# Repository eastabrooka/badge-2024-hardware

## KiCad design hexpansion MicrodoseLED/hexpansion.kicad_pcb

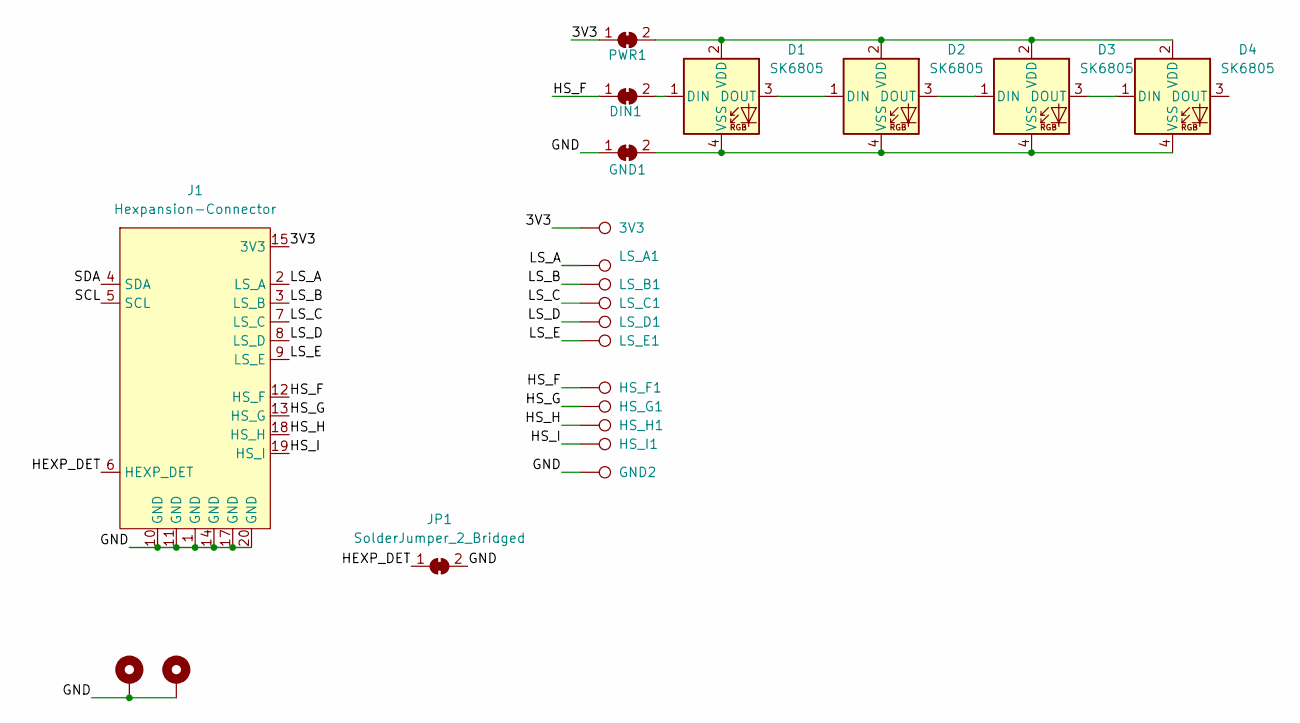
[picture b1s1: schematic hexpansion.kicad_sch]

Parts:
3V3: TestPoint; TestPoint_Pad_D1.0mm
D1, D2, D3, D4: SK6805; SK6805-EC15
DIN1: SolderJumper_2_Bridged; SolderJumper-2_P1.3mm_Bridged_RoundedPad1.0x1.5mm
GND1: SolderJumper_2_Bridged; SolderJumper-2_P1.3mm_Bridged_RoundedPad1.0x1.5mm
GND2: TestPoint; TestPoint_Pad_D1.0mm
H1, H2: MountingHole_Pad; MountingHole_2.2mm_M2_Pad_Via
HS_F1: TestPoint; TestPoint_Pad_D1.0mm
HS_G1: TestPoint; TestPoint_Pad_D1.0mm
HS_H1: TestPoint; TestPoint_Pad_D1.0mm
HS_I1: TestPoint; TestPoint_Pad_D1.0mm
J1: Hexpansion-Connector; hexpansion-edge-connector
JP1: SolderJumper_2_Bridged; SolderJumper-2_P1.3mm_Bridged_RoundedPad1.0x1.5mm
LS_A1: TestPoint; TestPoint_Pad_D1.0mm
LS_B1: TestPoint; TestPoint_Pad_D1.0mm
LS_C1: TestPoint; TestPoint_Pad_D1.0mm
LS_D1: TestPoint; TestPoint_Pad_D1.0mm
LS_E1: TestPoint; TestPoint_Pad_D1.0mm
PWR1: SolderJumper_2_Bridged; SolderJumper-2_P1.3mm_Bridged_RoundedPad1.0x1.5mm

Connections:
/3V3: 3V3.1, J1.15 (3V3), J1.16 (3V3), PWR1.1 (A)
/GND: GND1.1 (A), GND2.1, H1.1, H2.1, J1.1 (GND), J1.10 (GND), J1.11 (GND), J1.14 (GND), J1.17 (GND), J1.20 (GND), JP1.2 (B)
/HEXP_DET: J1.6 (HEXP_DET), JP1.1 (A)
/HS_F: DIN1.1 (A), HS_F1.1, J1.12 (HS_F)
/HS_G: HS_G1.1, J1.13 (HS_G)
/HS_H: HS_H1.1, J1.18 (HS_H)
/HS_I: HS_I1.1, J1.19 (HS_I)
/LS_A: J1.2 (LS_A), LS_A1.1
/LS_B: J1.3 (LS_B), LS_B1.1
/LS_C: J1.7 (LS_C), LS_C1.1
/LS_D: J1.8 (LS_D), LS_D1.1
/LS_E: J1.9 (LS_E), LS_E1.1
/SCL: J1.5 (SCL)
/SDA: J1.4 (SDA)
unnamed: D1.1 (DIN), DIN1.2 (B)
unnamed: D1.3 (DOUT), D2.1 (DIN)
unnamed: D1.2 (VDD), D2.2 (VDD), D3.2 (VDD), D4.2 (VDD), PWR1.2 (B)
unnamed: D1.4 (VSS), D2.4 (VSS), D3.4 (VSS), D4.4 (VSS), GND1.2 (B)
unnamed: D2.3 (DOUT), D3.1 (DIN)
unnamed: D3.3 (DOUT), D4.1 (DIN)

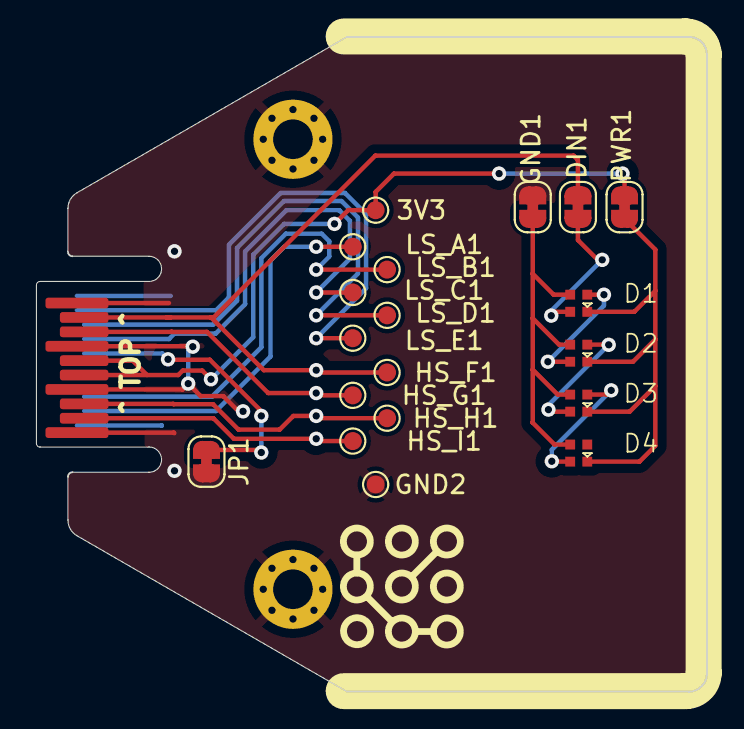
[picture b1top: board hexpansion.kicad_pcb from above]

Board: 2 copper layers, 37.2 x 36.4 mm, 22 parts (0 on the bottom side), 18 nets.

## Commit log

2024-08-04 Make LED Test Board.
